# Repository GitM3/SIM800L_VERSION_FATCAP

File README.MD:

# GDRT 2023
- Sourcecode for Pi Pico
- PCB schematics in PCB folder

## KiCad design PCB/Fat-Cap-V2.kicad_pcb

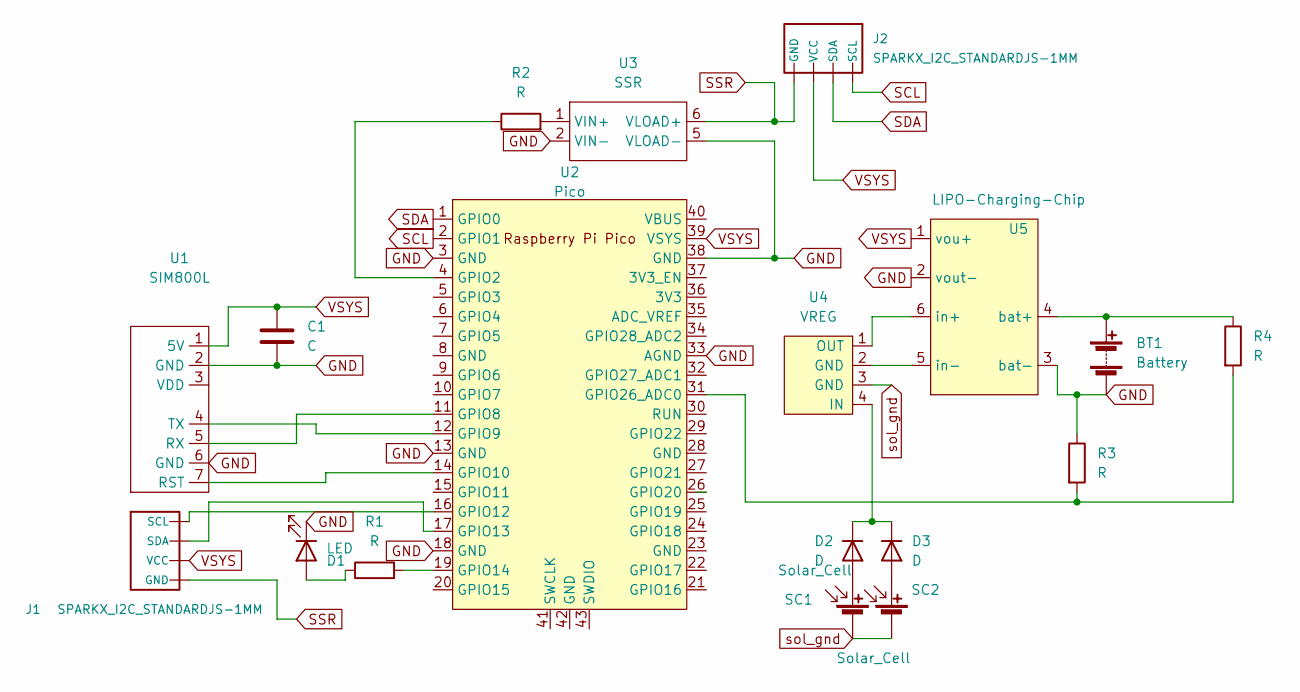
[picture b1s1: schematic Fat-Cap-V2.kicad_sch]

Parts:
BT1: Battery; JST-2-M
C1: C; CAP
D1: LED
D2, D3: D; Resistor
J1, J2: SPARKX_I2C_STANDARDJS-1MM; JST-4PIN-M
R1, R2, R3, R4: R; Resistor
SC1, SC2: Solar_Cell; 2155 Connector
U1: SIM800L; SIM800
U2: Pico; RPi_Pico_SMD_TH
U3: SSR; AQV252G
U4: VREG; V-Regulator
U5: LIPO-Charging-Chip; CHRG1

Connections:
GND: BT1.2 (-), C1.1, D1.1 (K), R3.1, U1.2 (GND), U1.6 (GND), U2.3 (GND), U2.13 (GND), U2.18 (GND), U2.33 (AGND), U2.38 (GND), U3.2 (VIN-), U3.5 (VLOAD-), U5.2 (vout-), U5.3 (bat-); also elsewhere on the board
unnamed: BT1.1 (+), R4.1, U5.4 (bat+)
unnamed: D1.2 (A), R1.1
unnamed: D2.1 (K), D3.1 (K), U4.4 (IN)
unnamed: D2.2 (A), SC1.1 (+)
unnamed: D3.2 (A), SC2.1 (+)
unnamed: J1.3 (SDA), U2.17 (GPIO13)
unnamed: J1.4 (SCL), U2.16 (GPIO12)
unnamed: R1.2, U2.19 (GPIO14)
unnamed: R2.1, U2.4 (GPIO2)
unnamed: R2.2, U3.1 (VIN+)
unnamed: R3.2, R4.2, U2.31 (GPIO26_ADC0)
unnamed: U1.4 (TX), U2.12 (GPIO9)
unnamed: U1.5 (RX), U2.11 (GPIO8)
unnamed: U1.7 (RST), U2.14 (GPIO10)
unnamed: U4.1 (OUT), U5.6 (in+)
unnamed: U4.2 (GND), U5.5 (in-)
SCL: J2.4 (SCL), U2.2 (GPIO1)
SDA: J2.3 (SDA), U2.1 (GPIO0)
SSR: J1.1 (GND), J2.1 (GND), U3.6 (VLOAD+)
VSYS: C1.2, J1.2 (VCC), J2.2 (VCC), U1.1 (5V), U2.39 (VSYS), U5.1 (vou+)
sol_gnd: SC1.GND (-), SC2.GND (-), U4.3 (GND)

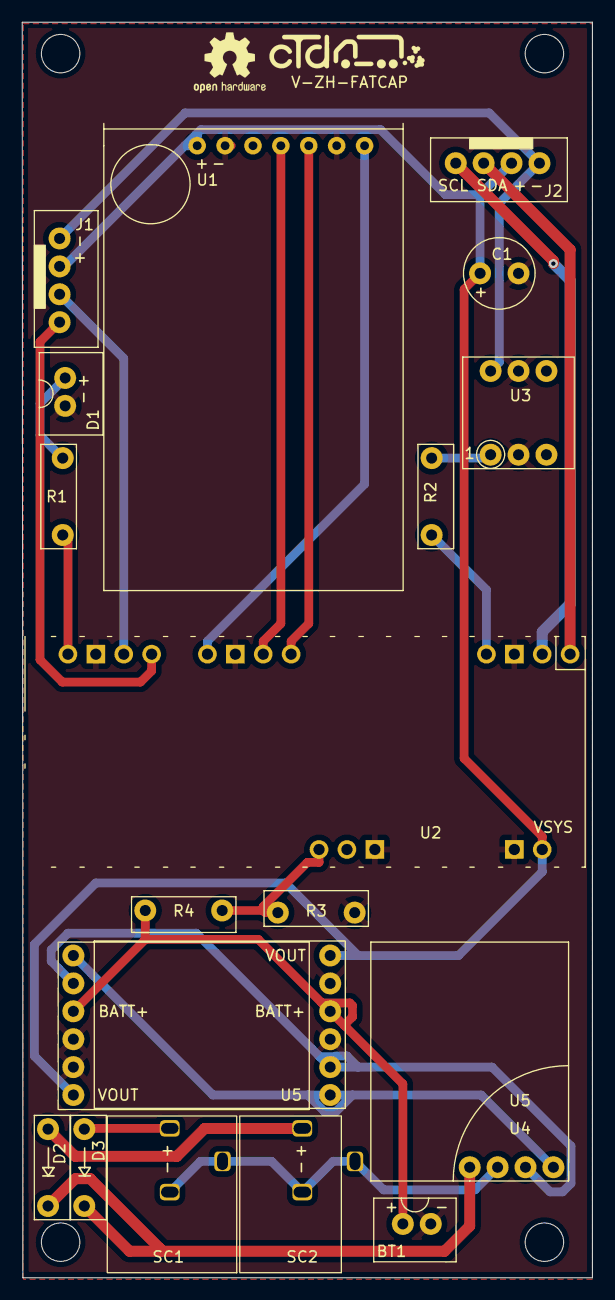
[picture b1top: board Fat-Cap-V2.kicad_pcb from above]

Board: 2 copper layers, 51.9 x 114.3 mm, 19 parts (0 on the bottom side), 22 nets.

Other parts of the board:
U5#2: CHRG; CHRG_2

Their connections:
GND: U5#2.2 (vout-), U5#2.3 (bat-); also elsewhere on the board

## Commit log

2022-11-07 Created Readme.md
2023-08-01 Added PCB files
2023-08-01 Added unique device ID
